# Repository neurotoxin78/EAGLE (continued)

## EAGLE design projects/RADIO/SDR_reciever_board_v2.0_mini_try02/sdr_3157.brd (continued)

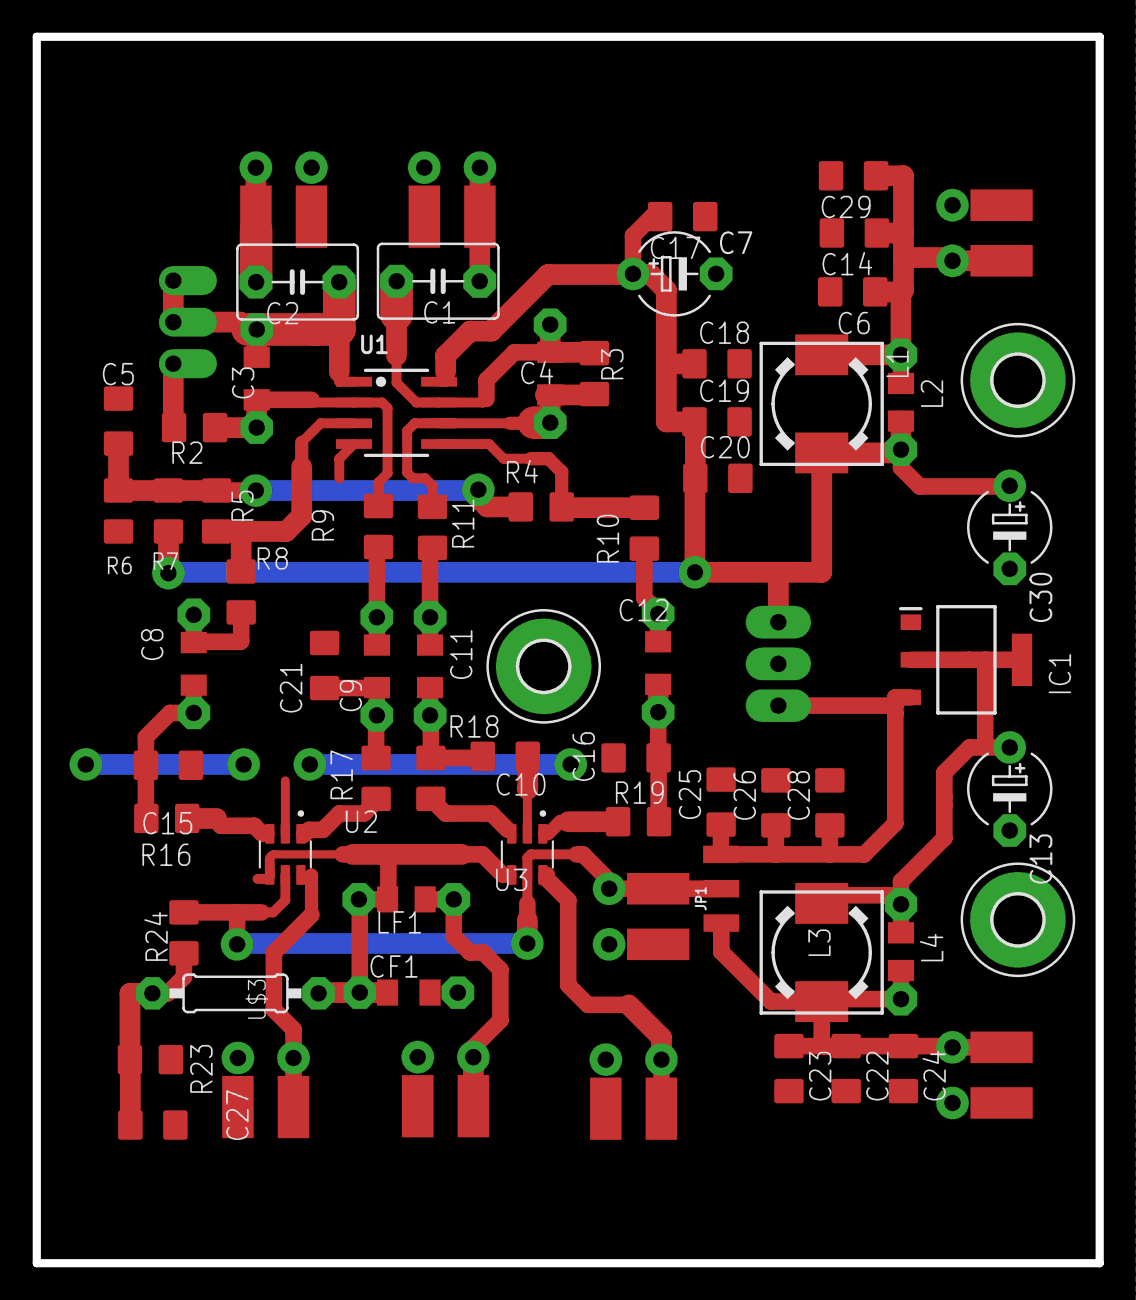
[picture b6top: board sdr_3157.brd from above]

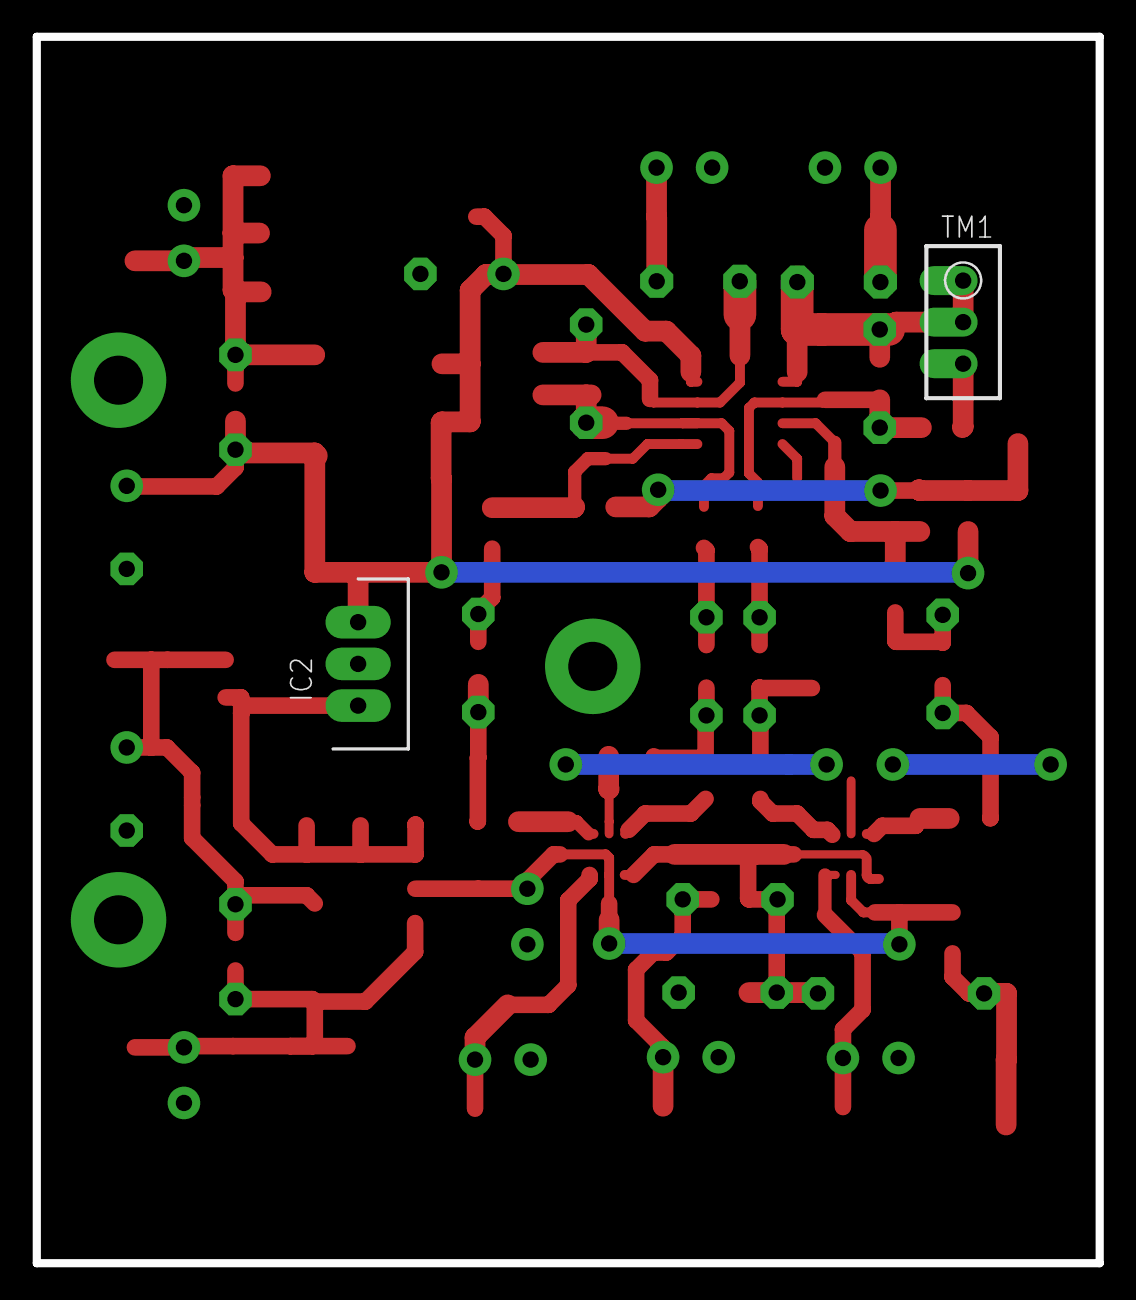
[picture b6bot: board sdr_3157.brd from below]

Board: 2 copper layers, 65.0 x 75.0 mm, 71 parts (2 on the bottom side), 34 nets.

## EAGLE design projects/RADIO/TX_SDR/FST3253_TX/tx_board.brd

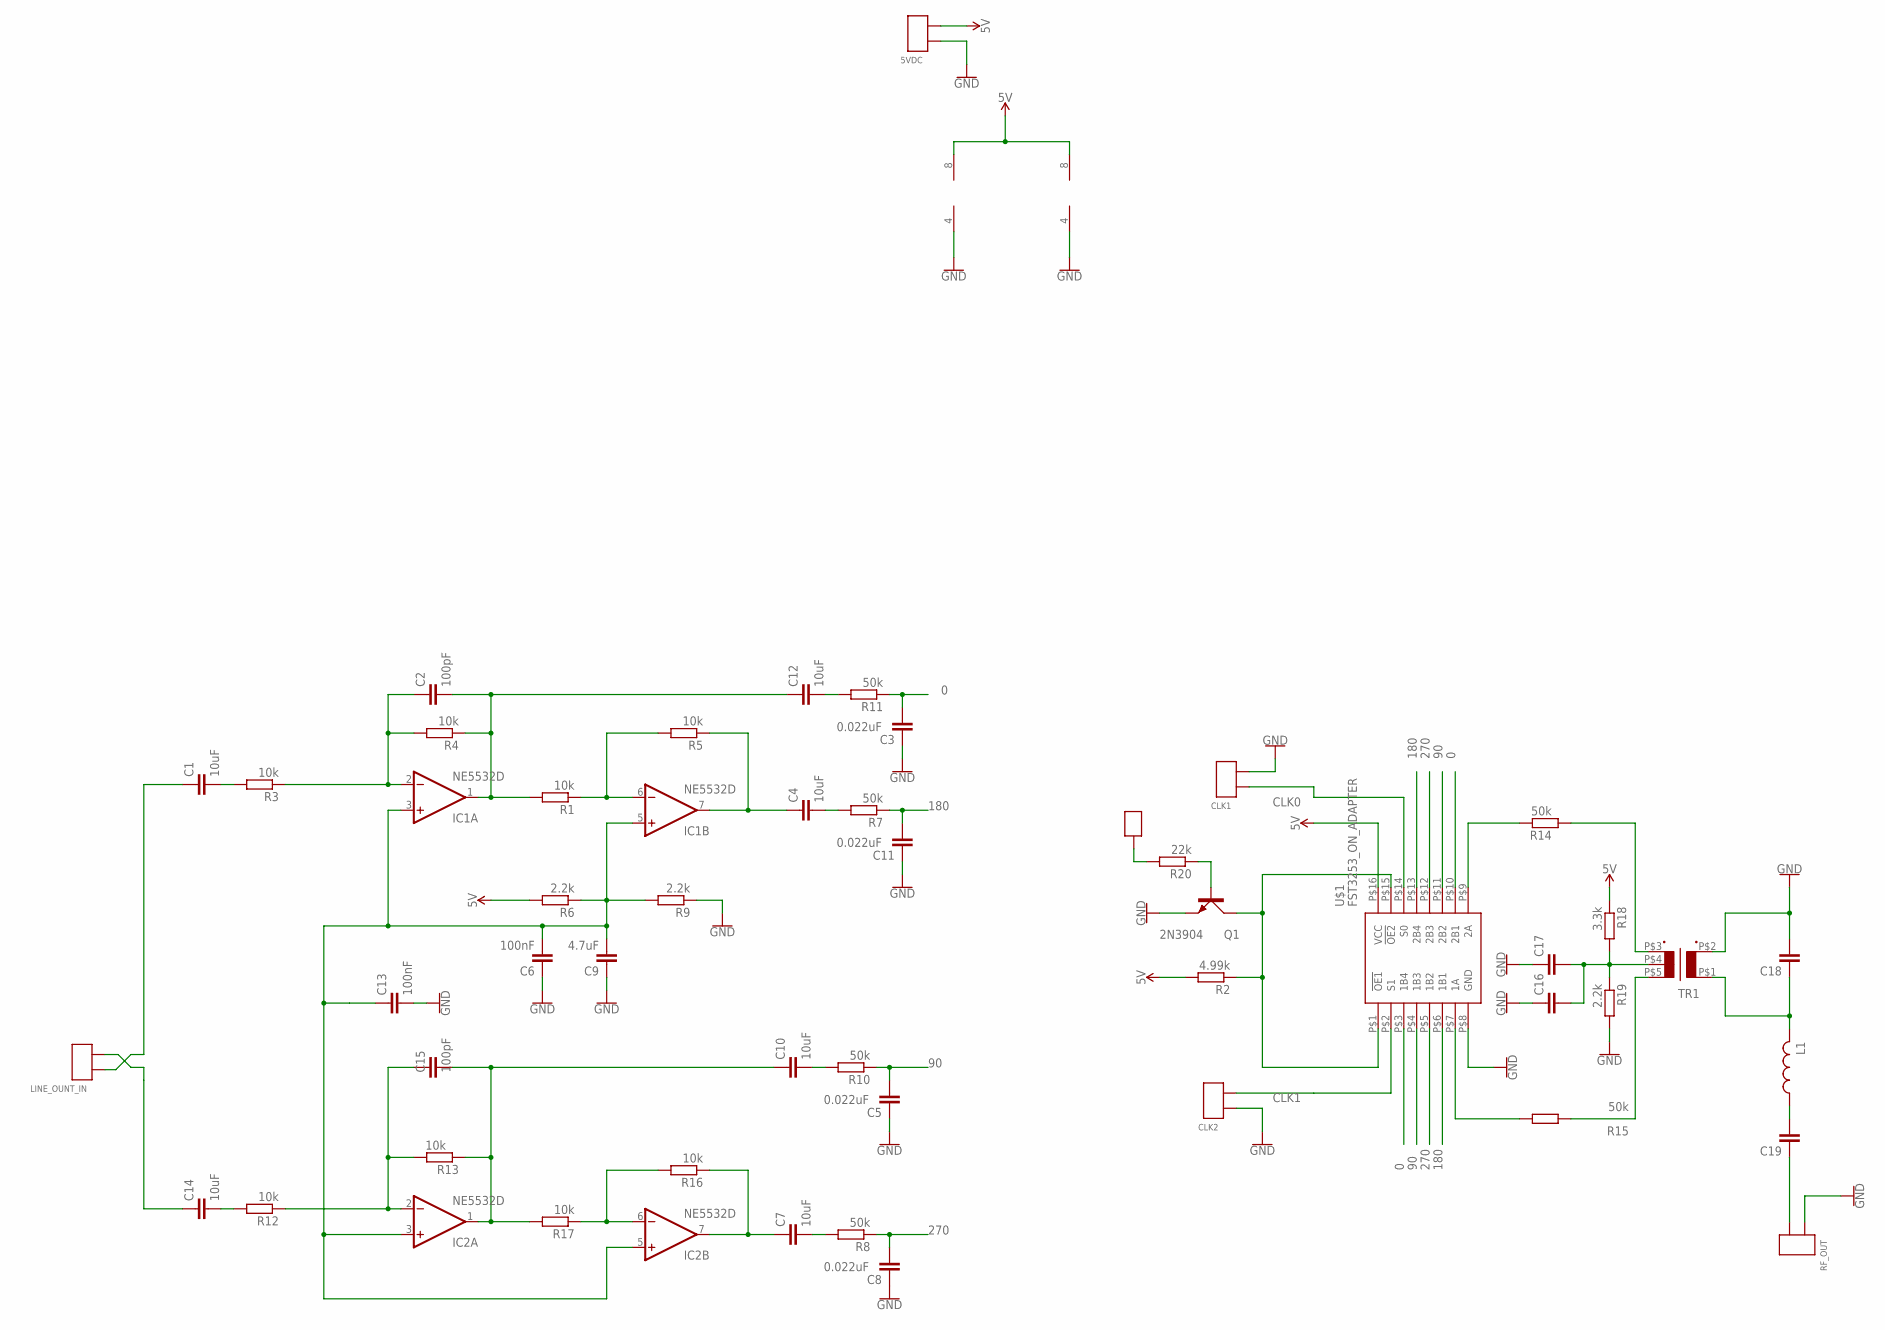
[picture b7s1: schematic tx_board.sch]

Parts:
5VDC: 2X_SMD_PTH_PIN; 2X_SMD_PTH
C1, C4, C7, C10, C12, C14: 10uF; C0805
C2, C15: 100pF; C0805
C3, C5, C8, C11: 0.022uF; C0805
C6, C13: 100nF; C0805
C9: 4.7uF; C0805
C16, C17: C_0805_SMD; C0805
C18, C19: C_0805_PTH; C0805K
CLK1, CLK2: 2X_SMD_PTH_PIN; 2X_SMD_PTH
IC1, IC2: NE5532D; SO08
L1: L_0805_PTH; M0805
LINE_OUNT_IN: 2X_SMD_PTH_PIN; 2X_SMD_PTH
Q1: 2N3904; TO92D
R1, R3, R4, R5, R12, R13, R16, R17: 10k; R0805W
R2: 4.99k; R0805W
R6: 2.2k; 0204/7
R7, R8, R10, R11, R14, R15: 50k; R0805W
R9, R19: 2.2k; R0805W
R18: 3.3k; R0805W
R20: 22k; R0805W
RF_OUT: 2X_SMD_PTH_PIN; 2X_SMD_PTH
TR1: 5PIN_TRANSFORMER
TX_DISABLE: SMD_PTH_PIN
U$1: FST3253_ON_ADAPTER; SSOP16_ADAPTER

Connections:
0: C3.2, R11.1, R11.P$1, U$1.P$3 (1B4), U$1.P$10 (2B1)
5V: 5VDC.P$2 (PIN1), 5VDC.T$2 (PIN1), IC1.8 (V+), IC2.8 (V+), R2.2, R6.2, R18.1, U$1.P$16 (VCC); also elsewhere on the board
90: C5.2, R10.1, R10.P$1, U$1.P$4 (1B3), U$1.P$11 (2B2)
180: C11.2, R7.1, R7.P$1, U$1.P$6 (1B1), U$1.P$13 (2B4)
270: C8.2, R8.1, R8.P$1, U$1.P$5 (1B2), U$1.P$12 (2B3)
GND: 5VDC.P$1 (PIN0), 5VDC.T$1 (PIN0), C3.1, C5.1, C6.1, C8.1, C9.1, C11.1, C13.2, C16.1, C17.1, C17.P$1, C18.2, C18.P$2 (2), CLK1.P$2 (PIN1), CLK1.T$2 (PIN1), CLK2.P$1 (PIN0), IC1.4 (V-), IC2.4 (V-), Q1.E, R9.1, R19.2, RF_OUT.P$1 (PIN0), RF_OUT.T$1 (PIN0), TR1.P$2 (2), U$1.P$8 (GND); also elsewhere on the board
unnamed: Q1.C, R2.1, U$1.P$1 (!OE1), U$1.P$15 (!OE2)
unnamed: R15.2, R15.P$2, U$1.P$7 (1A)
unnamed: R14.2, R14.P$2, U$1.P$9 (2A)
unnamed: R14.1, R14.P$1, TR1.P$3 (3)
unnamed: R15.1, R15.P$1, TR1.P$5 (5)
unnamed: C16.2, C17.2, C17.P$2, R18.2, R19.1, TR1.P$4 (4)
unnamed: C2.1, C2.P$1, IC1.2 (-IN), R3.1, R3.P$1, R4.2, R4.P$2
unnamed: C18.1, C18.P$1 (1), L1.2, L1.P$2 (2), TR1.P$1 (1)
unnamed: C19.2, C19.P$2 (2), L1.1, L1.P$1 (1)
unnamed: C2.2, C2.P$2, C12.1, C12.P$1, IC1.1 (OUT), R1.2, R1.P$2, R4.1, R4.P$1
unnamed: IC1.6 (-IN), R1.1, R1.P$1, R5.2
unnamed: C15.1, C15.P$1, IC2.2 (-IN), R12.1, R12.P$1, R13.2, R13.P$2
unnamed: C10.1, C10.P$1, C15.2, C15.P$2, IC2.1 (OUT), R13.1, R13.P$1, R17.2, R17.P$2
unnamed: IC2.6 (-IN), R16.2, R16.P$2, R17.1, R17.P$1
unnamed: C4.1, C4.P$1, IC1.7 (OUT), R5.1
unnamed: C7.1, C7.P$1, IC2.7 (OUT), R16.1, R16.P$1
unnamed: C4.2, C4.P$2, R7.2, R7.P$2
unnamed: C19.1, C19.P$1 (1), RF_OUT.P$2 (PIN1), RF_OUT.T$2 (PIN1)
unnamed 24: C1.1, C1.P$1, LINE_OUNT_IN.P$1 (PIN0); also elsewhere on the board
unnamed 25: C14.1, C14.P$1, LINE_OUNT_IN.P$2 (PIN1); also elsewhere on the board
unnamed: Q1.B, R20.1
unnamed: C14.2, C14.P$2, R12.2, R12.P$2
unnamed: C1.2, C1.P$2, R3.2, R3.P$2
unnamed: R20.2, TX_DISABLE.P$1
unnamed: C12.2, C12.P$2, R11.2, R11.P$2
unnamed: C10.2, C10.P$2, R10.2, R10.P$2
unnamed: C7.2, C7.P$2, R8.2, R8.P$2
unnamed: C6.2, C9.2, C13.1, IC1.3 (+IN), IC1.5 (+IN), IC2.3 (+IN), IC2.5 (+IN), R6.1, R9.2

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
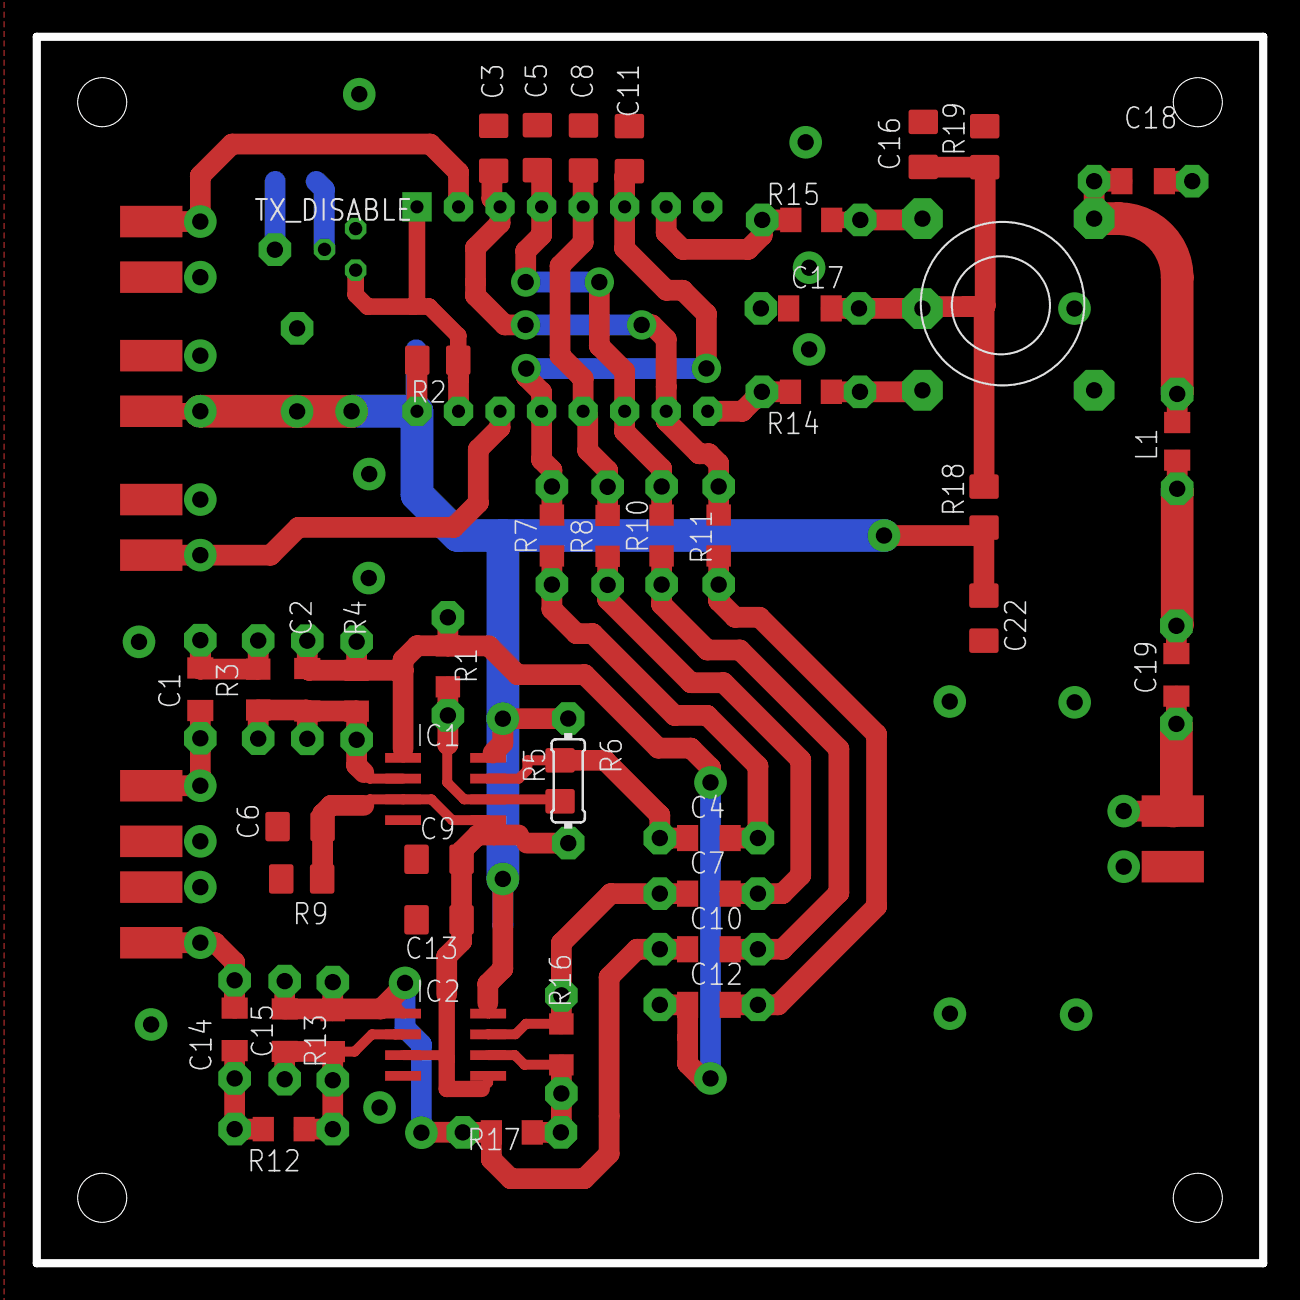
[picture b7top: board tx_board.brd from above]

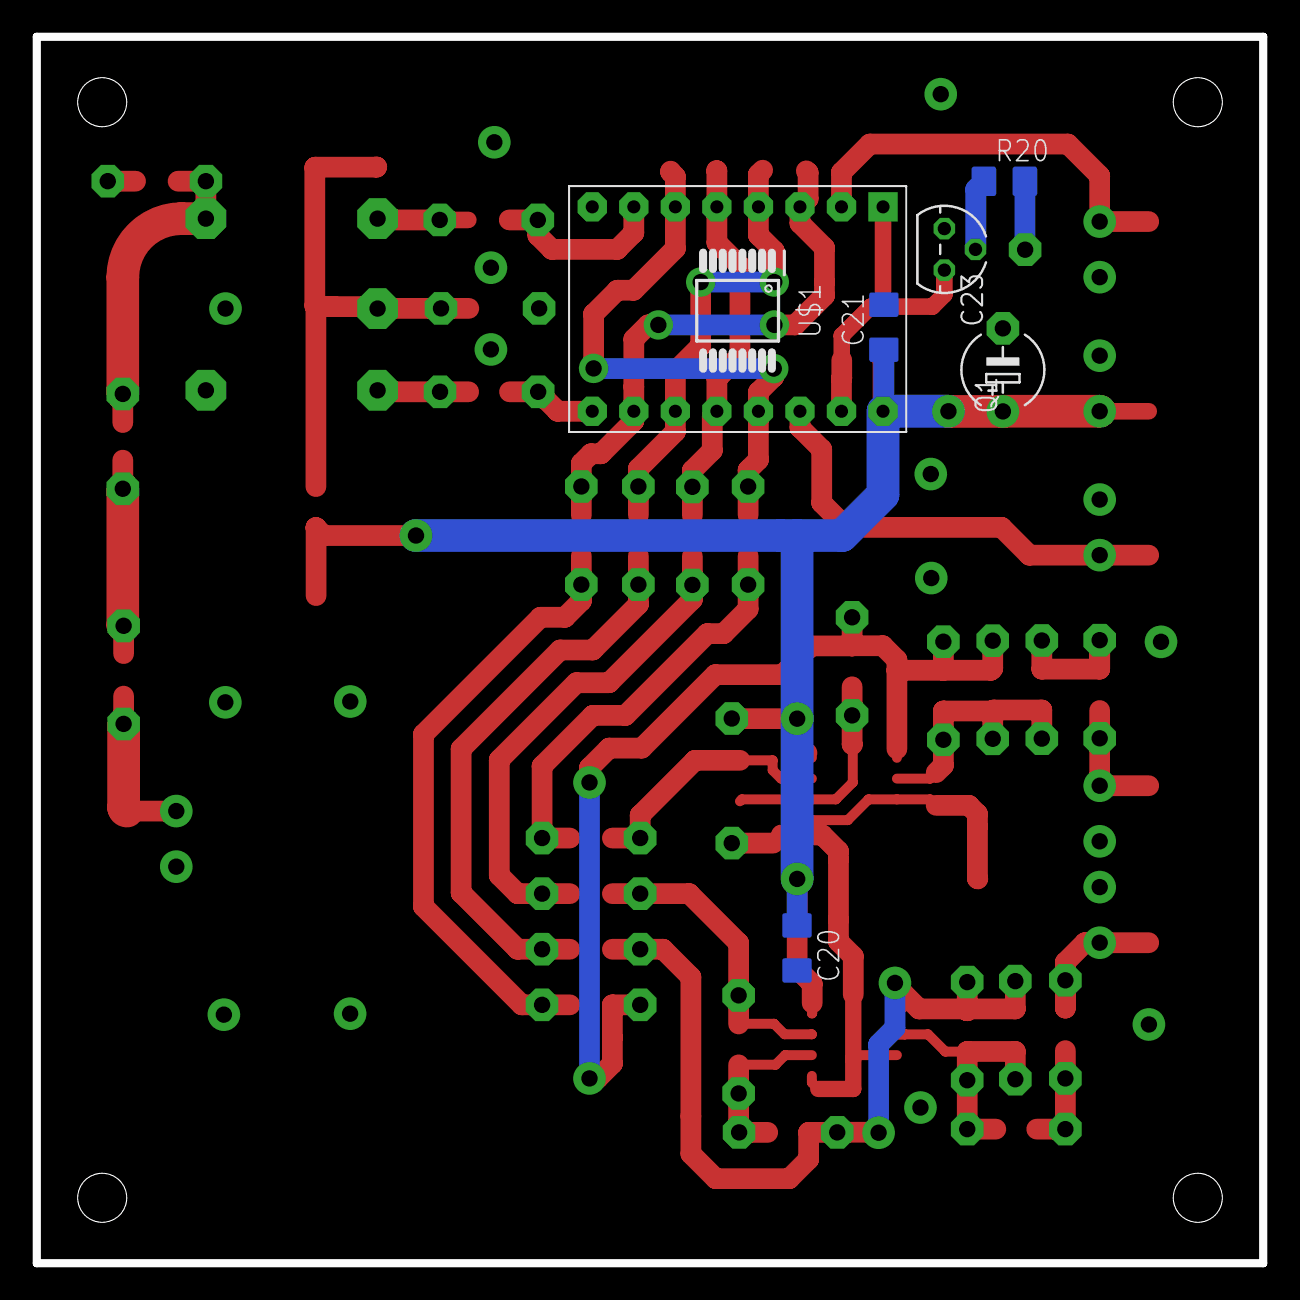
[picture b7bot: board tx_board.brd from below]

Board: 2 copper layers, 75.0 x 75.0 mm, 56 parts (6 on the bottom side), 36 nets.

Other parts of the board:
C20, C21, C22: C0805
C23: E5-5
CLK0: 2X_SMD_PTH_PIN; 2X_SMD_PTH
LINE_OUT_IN_L: 2X_SMD_PTH_PIN; 2X_SMD_PTH
LINE_OUT_IN_R: 2X_SMD_PTH_PIN; 2X_SMD_PTH

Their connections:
5V: C20.1, C21.1, C22.1, C23.+; also elsewhere on the board
GND: C20.2, C21.2, C22.2, C23.-, CLK0.P$1, CLK0.T$1, LINE_OUT_IN_L.P$1, LINE_OUT_IN_L.T$1, LINE_OUT_IN_R.P$2, LINE_OUT_IN_R.T$2; also elsewhere on the board
unnamed 24: LINE_OUT_IN_R.P$1, LINE_OUT_IN_R.T$1; also elsewhere on the board
unnamed 25: LINE_OUT_IN_L.P$2, LINE_OUT_IN_L.T$2; also elsewhere on the board
